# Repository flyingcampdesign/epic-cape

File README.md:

*STATUS:* The initial prototype PCB for this cape has been manufactured and is in the bring up phase.  A couple issues have been found that will require a new pcb spin.  Please do not fork this project until these issues have been fixed!  Check out <http://twitter.com/FlyingCamp> for updates on bring-up and test.

The Epic Cape is a cape for the BeagleBone that adds an 802.15.4 wireless mesh networking interface.  

The Epic Cape uses the open source Epic module (http://www.cs.berkeley.edu/~prabal/projects/epic/) which allows the cape to act as a compact egress router for low power sensor networks.  The Epic module is fully supported by the open source TinyOS (http://www.tinyos.net) sensor network operating system and features a complete 6lowpan/RPL IPv6 stack (http://docs.tinyos.net/tinywiki/index.php/BLIP_2.0) that allows transmission of IPv6 Packets over IEEE 802.15.4 networks.  The Epic Cape will allow you to develop an 802.15.4 wireless sensor network with IPv6 connectivity to each low power mesh endpoint.

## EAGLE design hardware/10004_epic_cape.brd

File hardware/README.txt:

Eagle Zip Release
=============

* Save board and schematic
* Create schematic PDF (<proj name>.pdf)
* Create BOM file (<proj name>.xlsx)
    * In schematic editor, execute "run bom.ulp"
    * Change "List Type" to "Values"
    * Change "Output Format" to "CSV"
    * "Save" as <proj name>.csv
    * Use Excel to convert to <proj name>.xlsx
* Execute "make eagle"

Fab Zip Release
===============

* Complete "Eagle Zip Release" steps
* Run CAM processor to generate Gerber files
* Create XYRS pick-n-place files
    * In layout editor, execute "run mountsmd.ulp"
    * Save as <proj name>.mnt and <proj name>.mnb
* Create photoplots PDF (<proj name>_photoplots.pdf)
* Execute "make fab"

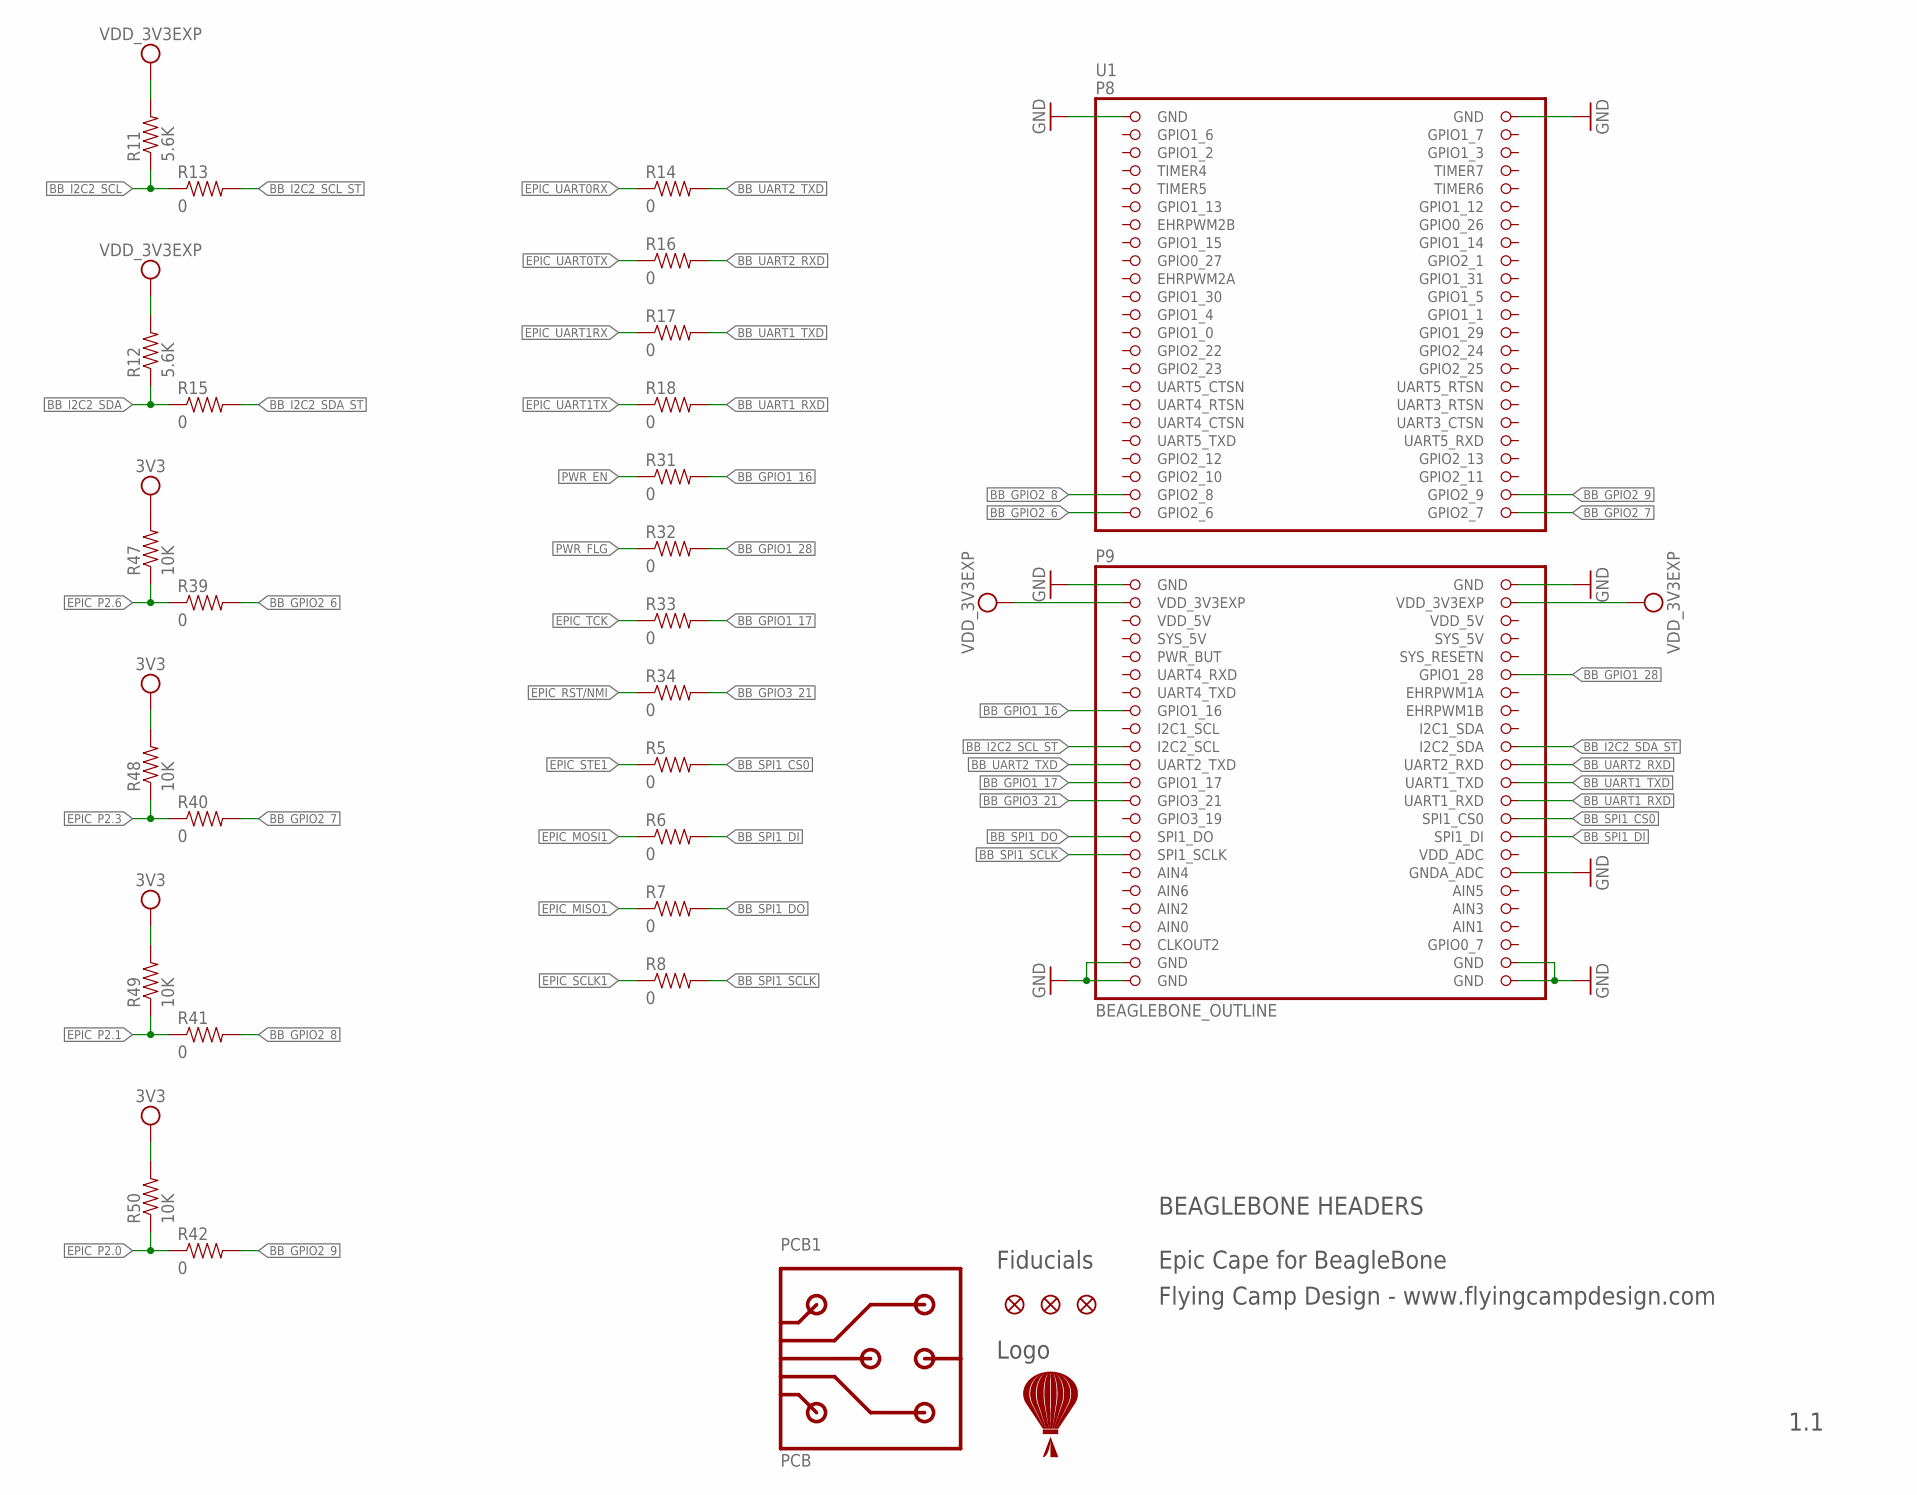
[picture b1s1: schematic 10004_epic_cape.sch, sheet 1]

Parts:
R5, R6, R7, R8, R13, R14, R15, R16, R17, R18, R31, R32, R33, R34, R39, R40, R41, R42: 0; RESC1005; MPN ERJ-2GE0R00X
R11, R12: 5.6K; RESC1005; MPN ERJ-2RKF5601X
R47, R48, R49, R50: 10K; RESC1005; MPN ERJ-2RKF1002X
U1: BEAGLEBONE_OUTLINE; BEAGLEBONE_SHIELD
U$2: LOGO
U$3, U$4, U$5: FIDUCIAL1X2.5; FIDUCIAL-1X2.5

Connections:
3V3: R47.2, R48.2, R49.2, R50.2; also elsewhere on the board
AIN0: U1.85 (AIN0)
AIN3: U1.84 (AIN3)
BB_GPIO1_16: R31.2, U1.61 (GPIO1_16)
BB_GPIO1_17: R33.2, U1.69 (GPIO1_17)
BB_GPIO1_28: R32.2, U1.58 (GPIO1_28)
BB_GPIO2_6: R39.2, U1.45 (GPIO2_6)
BB_GPIO2_7: R40.2, U1.46 (GPIO2_7)
BB_GPIO2_8: R41.2, U1.43 (GPIO2_8)
BB_GPIO2_9: R42.2, U1.44 (GPIO2_9)
BB_GPIO3_21: R34.2, U1.71 (GPIO3_21)
BB_I2C2_SCL: R11.1, R13.1; also elsewhere on the board
BB_I2C2_SCL_ST: R13.2, U1.65 (I2C2_SCL)
BB_I2C2_SDA: R12.1, R15.1; also elsewhere on the board
BB_I2C2_SDA_ST: R15.2, U1.66 (I2C2_SDA)
BB_SPI1_CS0: R5.2, U1.74 (SPI1_CS0)
BB_SPI1_DI: R6.2, U1.76 (SPI1_DI)
BB_SPI1_DO: R7.2, U1.75 (SPI1_DO)
BB_SPI1_SCLK: R8.2, U1.77 (SPI1_SCLK)
BB_UART1_RXD: R18.2, U1.72 (UART1_RXD)
BB_UART1_TXD: R17.2, U1.70 (UART1_TXD)
BB_UART2_RXD: R16.2, U1.68 (UART2_RXD)
BB_UART2_TXD: R14.2, U1.67 (UART2_TXD)
EPIC_MISO1: R7.1; also elsewhere on the board
EPIC_MOSI1: R6.1; also elsewhere on the board
EPIC_P2.0: R42.1, R50.1; also elsewhere on the board
EPIC_P2.1: R41.1, R49.1; also elsewhere on the board
EPIC_P2.3: R40.1, R48.1; also elsewhere on the board
EPIC_P2.6: R39.1, R47.1; also elsewhere on the board
EPIC_RST/NMI: R34.1; also elsewhere on the board
EPIC_SCLK1: R8.1; also elsewhere on the board
EPIC_STE1: R5.1; also elsewhere on the board
EPIC_TCK: R33.1; also elsewhere on the board
EPIC_UART0RX: R14.1; also elsewhere on the board
EPIC_UART0TX: R16.1; also elsewhere on the board
EPIC_UART1RX: R17.1; also elsewhere on the board
EPIC_UART1TX: R18.1; also elsewhere on the board
GND: U1.1 (GND), U1.2 (GND), U1.47 (GND), U1.48 (GND), U1.80 (GNDA_ADC), U1.89 (GND), U1.90 (GND), U1.91 (GND), U1.92 (GND); also elsewhere on the board
GPIO1_6: U1.3 (GPIO1_6)
GPIO1_7: U1.4 (GPIO1_7)
GPIO2_11: U1.42 (GPIO2_11)
PWR_EN: R31.1; also elsewhere on the board
PWR_FLG: R32.1; also elsewhere on the board
VDD_3V3EXP: R11.2, R12.2, U1.49 (VDD_3V3EXP), U1.50 (VDD_3V3EXP); also elsewhere on the board
VDD_5V: U1.51 (VDD_5V), U1.52 (VDD_5V)

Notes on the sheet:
Epic Cape for BeagleBone
Flying Camp Design - www.flyingcampdesign.com
1.1
Logo
Fiducials
BEAGLEBONE HEADERS

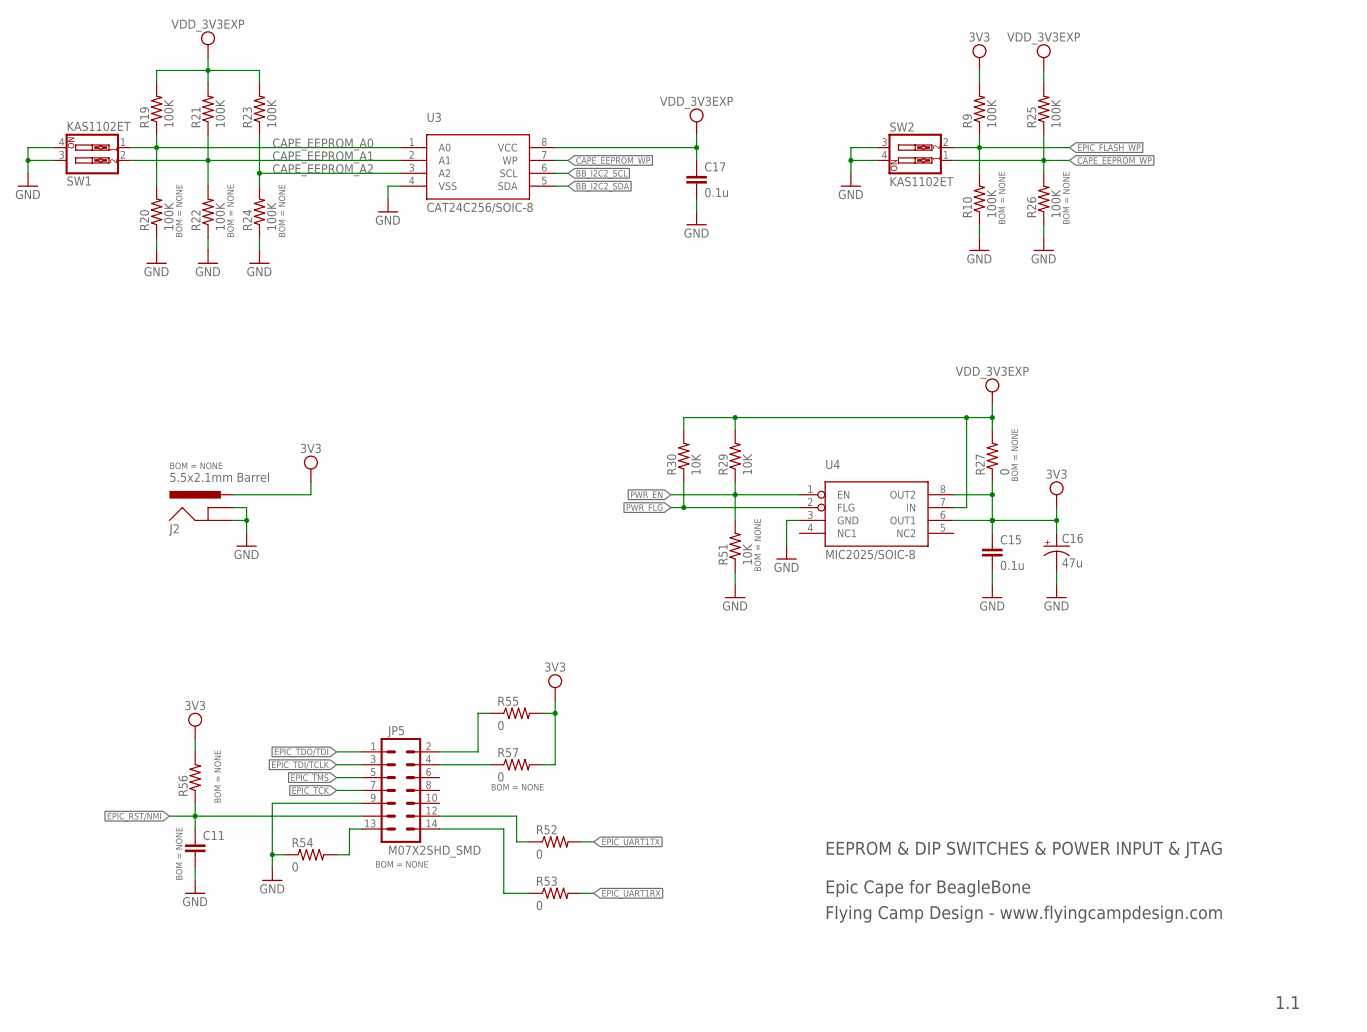
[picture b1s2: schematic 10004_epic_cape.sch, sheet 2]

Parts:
C11: CAPACITOR1005; CAPC1005
C15, C17: 0.1u; CAPC1005; MPN C0402C104K9RACTU
C16: 47u; EIA3216; MPN T491A476M006AT
J2: 5.5x2.1mm Barrel; POWER_JACK_SMD
JP5: M07X2SHD_SMD; 2X7-SHROUDED_SMD
R9, R10, R19, R20, R21, R22, R23, R24, R25, R26: 100K; RESC1005; MPN ERJ-2RKF1003X
R27: 0; RESC3216; MPN ERJ-8GEY0R00V
R29, R30, R51: 10K; RESC1005; MPN ERJ-2RKF1002X
R52, R53, R54, R55, R57: 0; RESC1005; MPN ERJ-2GE0R00X
R56: RESISTOR1005; RESC1005
SW1, SW2: KAS1102ET; DIPSWITCH-02; MPN KAS1102ET
U3: CAT24C256/SOIC-8; SOIC-8; MPN CAT24C256WI-GT3
U4: MIC2025/SOIC-8; SOIC-8; MPN MIC2025-1YM

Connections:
3V3: C15.1, C16.A (+), J2.VIN0 (PWR), R9.2, R27.1, R55.2, R56.2, R57.2, U4.6 (OUT1), U4.8 (OUT2); also elsewhere on the board
BB_I2C2_SCL: U3.6 (SCL); also elsewhere on the board
BB_I2C2_SDA: U3.5 (SDA); also elsewhere on the board
CAPE_EEPROM_A0: R19.1, R20.2, SW1.1, U3.1 (A0)
CAPE_EEPROM_A1: R21.1, R22.2, SW1.2, U3.2 (A1)
CAPE_EEPROM_A2: R23.1, R24.2, U3.3 (A2)
CAPE_EEPROM_WP: R25.1, R26.2, SW2.1, U3.7 (WP)
EPIC_FLASH_WP: R9.1, R10.2, SW2.2; also elsewhere on the board
EPIC_RST/NMI: C11.1, JP5.11, R56.1; also elsewhere on the board
EPIC_TCK: JP5.7; also elsewhere on the board
EPIC_TDI/TCLK: JP5.3; also elsewhere on the board
EPIC_TDO/TDI: JP5.1; also elsewhere on the board
EPIC_TMS: JP5.5; also elsewhere on the board
EPIC_UART1RX: R53.2; also elsewhere on the board
EPIC_UART1TX: R52.2; also elsewhere on the board
GND: C11.2, C15.2, C16.C (-), C17.2, J2.GND (GNDBREAK), J2.P$4 (GND), JP5.9, R10.1, R20.1, R22.1, R24.1, R26.1, R51.1, R54.1, SW1.3, SW1.4, SW2.3, SW2.4, U3.4 (VSS), U4.3 (GND); also elsewhere on the board
unnamed: JP5.13, R54.2
unnamed: JP5.12, R52.1
unnamed: JP5.14, R53.1
PWR_EN: R29.1, R51.2, U4.1 (EN); also elsewhere on the board
PWR_FLG: R30.1, U4.2 (FLG); also elsewhere on the board
VCCTARGET: JP5.4, R57.1
VCCTOOL: JP5.2, R55.1
VDD_3V3EXP: C17.1, R19.2, R21.2, R23.2, R25.2, R27.2, R29.2, R30.2, U3.8 (VCC), U4.7 (IN); also elsewhere on the board

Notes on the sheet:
Epic Cape for BeagleBone
Flying Camp Design - www.flyingcampdesign.com
1.1
EEPROM & DIP SWITCHES & POWER INPUT & JTAG

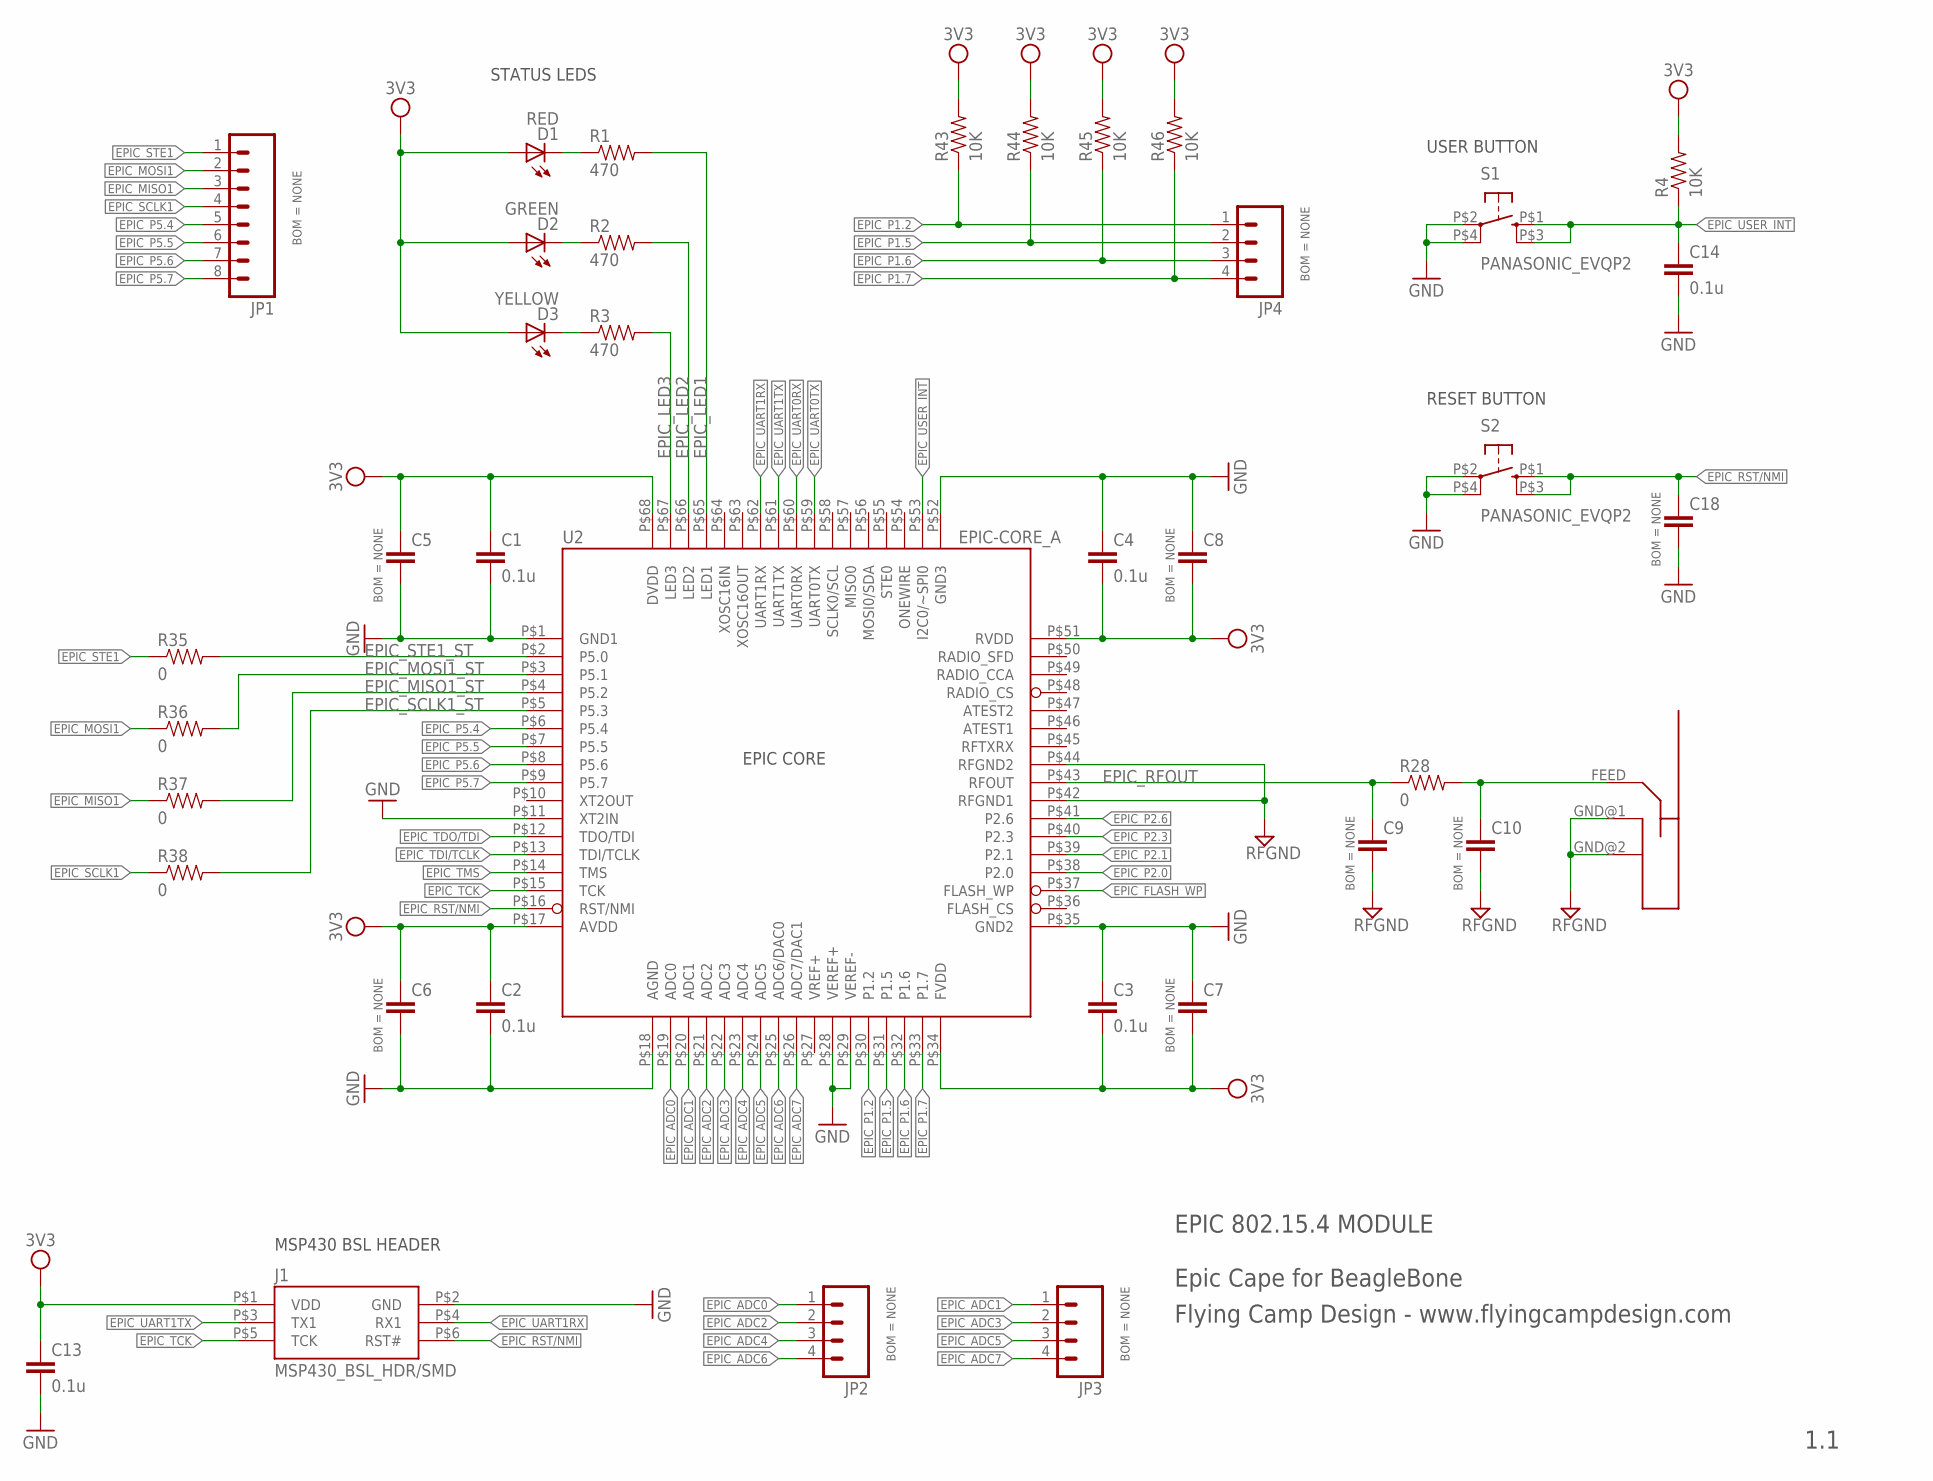
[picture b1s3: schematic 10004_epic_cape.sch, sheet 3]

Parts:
ANT1: 2.4GHZ_INVERTED_F_ANTENNA
C1, C2, C3, C4, C13, C14: 0.1u; CAPC1005; MPN C0402C104K9RACTU
C5, C6, C7, C8: CAPACITOR2012; CAPC2012
C9, C10, C18: CAPACITOR1005; CAPC1005
D1: RED; LEDC1608; MPN QTLP600C7TR
D2: GREEN; LEDC1608; MPN QTLP601C4TR
D3: YELLOW; LEDC1608; MPN QTLP600CYTR
J1: MSP430_BSL_HDR/SMD; HIROSE_DF11G-XXDP-2V; MPN DF11G-6DP-2V(50)
JP1: M081X08; 1X08
JP2, JP3, JP4: M04PTH; 1X04
R1, R2, R3: 470; RESC1005; MPN ERJ-2RKF4700X
R4, R43, R44, R45, R46: 10K; RESC1005; MPN ERJ-2RKF1002X
R28, R35, R36, R37, R38: 0; RESC1005; MPN ERJ-2GE0R00X
S1, S2: PANASONIC_EVQP2; MPN EVQ-P2K02Q
U2: EPIC-CORE_A; EPIC_LCC68; MPN EPIC-CORE-PCB

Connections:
3V3: C1.1, C2.1, C3.2, C4.2, C5.1, C6.1, C7.2, C8.2, C13.1, D1.A, D2.A, D3.A, J1.P$1 (VDD), R4.2, R43.2, R44.2, R45.2, R46.2, U2.P$17 (AVDD), U2.P$34 (FVDD), U2.P$51 (RVDD), U2.P$68 (DVDD); also elsewhere on the board
EPIC_ADC0: JP2.1, U2.P$19 (ADC0)
EPIC_ADC1: JP3.1, U2.P$20 (ADC1)
EPIC_ADC2: JP2.2, U2.P$21 (ADC2)
EPIC_ADC3: JP3.2, U2.P$22 (ADC3)
EPIC_ADC4: JP2.3, U2.P$23 (ADC4)
EPIC_ADC5: JP3.3, U2.P$24 (ADC5)
EPIC_ADC6: JP2.4, U2.P$25 (ADC6/DAC0)
EPIC_ADC7: JP3.4, U2.P$26 (ADC7/DAC1)
EPIC_FLASH_WP: U2.P$37 (FLASH_WP); also elsewhere on the board
EPIC_LED1: R1.2, U2.P$65 (LED1)
EPIC_LED2: R2.2, U2.P$66 (LED2)
EPIC_LED3: R3.2, U2.P$67 (LED3)
EPIC_MISO1: JP1.3, R37.1; also elsewhere on the board
EPIC_MISO1_ST: R37.2, U2.P$4 (P5.2)
EPIC_MOSI1: JP1.2, R36.1; also elsewhere on the board
EPIC_MOSI1_ST: R36.2, U2.P$3 (P5.1)
EPIC_P1.2: JP4.1, R43.1, U2.P$30 (P1.2)
EPIC_P1.5: JP4.2, R44.1, U2.P$31 (P1.5)
EPIC_P1.6: JP4.3, R45.1, U2.P$32 (P1.6)
EPIC_P1.7: JP4.4, R46.1, U2.P$33 (P1.7)
EPIC_P2.0: U2.P$38 (P2.0); also elsewhere on the board
EPIC_P2.1: U2.P$39 (P2.1); also elsewhere on the board
EPIC_P2.3: U2.P$40 (P2.3); also elsewhere on the board
EPIC_P2.6: U2.P$41 (P2.6); also elsewhere on the board
EPIC_P5.4: JP1.5, U2.P$6 (P5.4)
EPIC_P5.5: JP1.6, U2.P$7 (P5.5)
EPIC_P5.6: JP1.7, U2.P$8 (P5.6)
EPIC_P5.7: JP1.8, U2.P$9 (P5.7)
EPIC_RFOUT: C9.1, R28.1, U2.P$43 (RFOUT)
EPIC_RST/NMI: C18.1, J1.P$6 (RST#), S2.P$1 (1), S2.P$3 (3), U2.P$16 (RST/NMI); also elsewhere on the board
EPIC_SCLK1: JP1.4, R38.1; also elsewhere on the board
EPIC_SCLK1_ST: R38.2, U2.P$5 (P5.3)
EPIC_STE1: JP1.1, R35.1; also elsewhere on the board
EPIC_STE1_ST: R35.2, U2.P$2 (P5.0)
EPIC_TCK: J1.P$5 (TCK), U2.P$15 (TCK); also elsewhere on the board
EPIC_TDI/TCLK: U2.P$13 (TDI/TCLK); also elsewhere on the board
EPIC_TDO/TDI: U2.P$12 (TDO/TDI); also elsewhere on the board
EPIC_TMS: U2.P$14 (TMS); also elsewhere on the board
EPIC_UART0RX: U2.P$60 (UART0RX); also elsewhere on the board
EPIC_UART0TX: U2.P$59 (UART0TX); also elsewhere on the board
EPIC_UART1RX: J1.P$4 (RX1), U2.P$62 (UART1RX); also elsewhere on the board
EPIC_UART1TX: J1.P$3 (TX1), U2.P$61 (UART1TX); also elsewhere on the board
EPIC_USER_INT: C14.1, R4.1, S1.P$1 (1), S1.P$3 (3), U2.P$53 (I2C0/~SPI0)
FEED: ANT1.FEED, C10.1, R28.2
GND: C1.2, C2.2, C3.1, C4.1, C5.2, C6.2, C7.1, C8.1, C13.2, C14.2, C18.2, J1.P$2 (GND), S1.P$2 (2), S1.P$4 (4), S2.P$2 (2), S2.P$4 (4), U2.P$1 (GND1), U2.P$11 (XT2IN), U2.P$18 (AGND), U2.P$28 (VEREF+), U2.P$29 (VEREF-), U2.P$35 (GND2), U2.P$52 (GND3); also elsewhere on the board
unnamed: D1.C, R1.1
unnamed: D2.C, R2.1
unnamed: D3.C, R3.1
RFGND: ANT1.GND@1 (GND), ANT1.GND@2 (GND), C9.2, C10.2, U2.P$42 (RFGND1), U2.P$44 (RFGND2)

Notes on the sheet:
USER BUTTON
RESET BUTTON
STATUS LEDS
MSP430 BSL HEADER
Epic Cape for BeagleBone
Flying Camp Design - www.flyingcampdesign.com
1.1
EPIC CORE
EPIC 802.15.4 MODULE

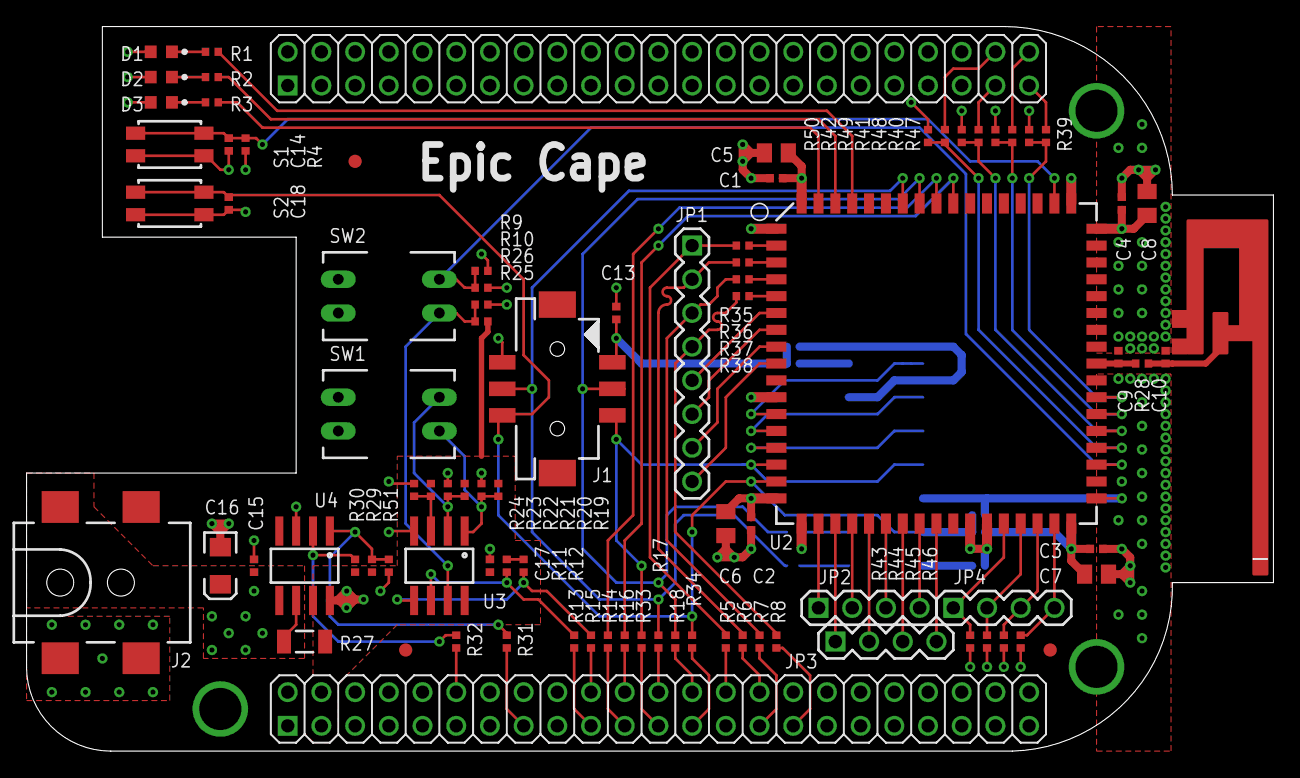
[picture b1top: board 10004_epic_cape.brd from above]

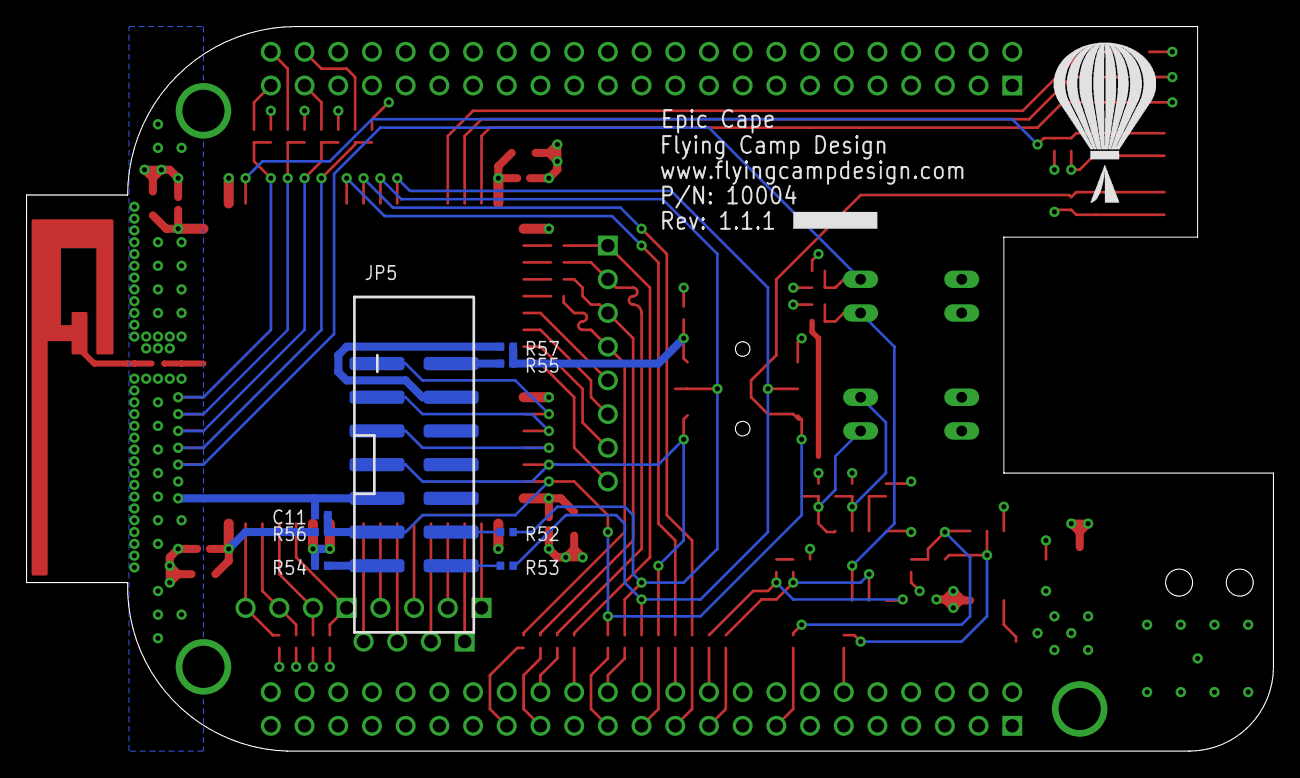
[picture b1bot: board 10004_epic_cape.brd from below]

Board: 4 copper layers, 94.0 x 54.6 mm, 97 parts (9 on the bottom side), 83 nets.

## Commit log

2013-01-01 Add Eagle schematic and board
2013-01-04 Update design
2013-01-05 Release 1.1.1
2013-01-05 Fix Makefile .PHONY
2013-01-05 Create gh-pages branch via GitHub
2013-01-05 Add layout image to Github pages
2013-01-09 Update status in readme
2013-01-09 Update PCB readme to match 66each.com specs

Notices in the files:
parts and their libraries:
SparkFun-Connectors: Licensing: CC v3.0 Share-Alike You are welcome to use this library for commercial purposes.
